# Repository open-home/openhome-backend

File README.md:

# OpenHome Backend

# Build
Run `npm run build` to build the backend.

# Running server
Navigate to `/dist` folder and run `node openhome-service.js`

# Docker deployment
Run `docker build -t image-name .` to build an image

Then you can get your container running:

`docker run -d -p 8080:8080 -p 3000:3000 -p 3001:3001 --name container-name image-name`

# Docker-compose deployment
Run `npm run-script docker` or `docker-compose up -d` to start the cluster of `openhome-backend` and `openhome-panel`

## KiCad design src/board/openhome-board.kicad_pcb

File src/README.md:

# OpenHome Backend

# Build
Run `npm run build` to build the backend.

# Running server
Navigate to `/dist` folder and run `node openhome-service.js`

# Docker deployment
Run `docker build -t image-name .` to build an image

Then you can get your container running:

`docker run -d -p 8080:8080 -p 3000:3000 -p 3001:3001 --name container-name image-name`

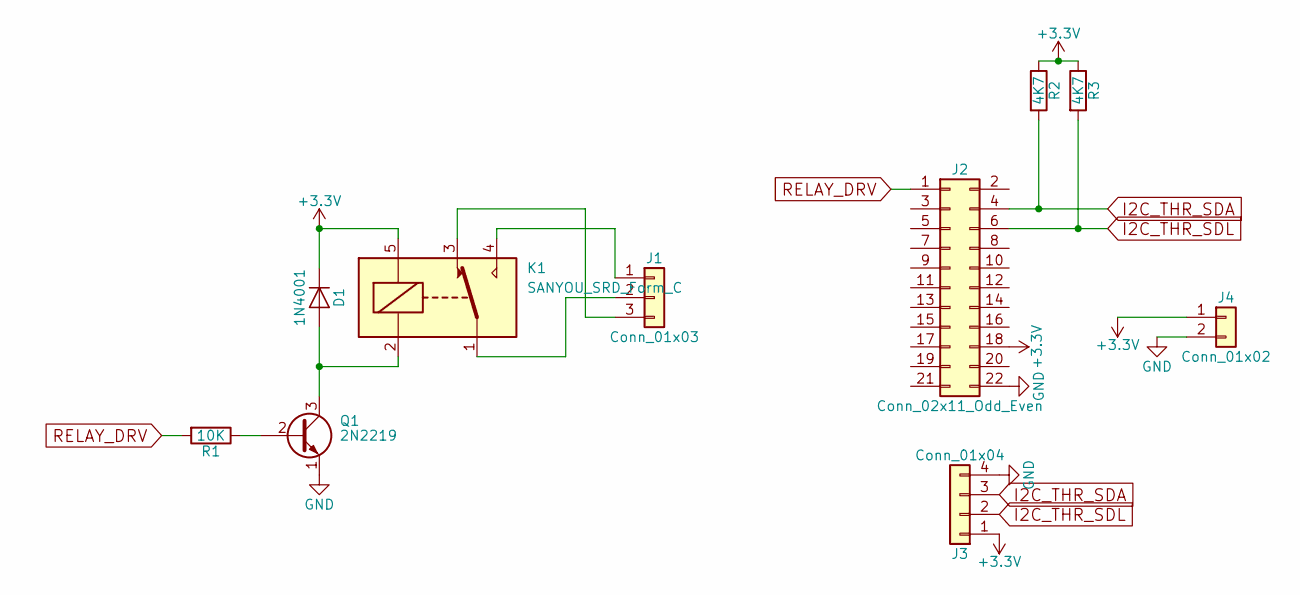
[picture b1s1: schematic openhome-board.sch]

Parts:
D1: 1N4001; D_DO-41_SOD81_Horizontal_RM10
J1: Conn_01x03; bornier3
J2: Conn_02x11_Odd_Even; ESPRUINO_WIFI
J3: Conn_01x04; SL-104-X-XX_1x04
J4: Conn_01x02
K1: SANYOU_SRD_Form_C; Relay_SPDT_SANYOU_SRD_Series_Form_C
Q1: 2N2219; TO-39-3
R1: 10K; R_Axial_DIN0207_L6.3mm_D2.5mm_P10.16mm_Horizontal
R2, R3: 4K7; R_Axial_DIN0207_L6.3mm_D2.5mm_P10.16mm_Horizontal

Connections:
+3V3: D1.1 (K), J2.18, J3.1, J4.1, K1.5, R2.1, R3.1
GND: J2.22, J3.4, J4.2, Q1.1 (E)
I2C_THR_SDA: J2.4, J3.3, R2.2
I2C_THR_SDL: J2.6, J3.2, R3.2
unnamed: D1.2 (A), K1.2, Q1.3 (C)
unnamed: J1.1, K1.4
unnamed: J1.2, K1.1
unnamed: J1.3, K1.3
unnamed: Q1.2 (B), R1.1
RELAY_DRV: J2.1, R1.2

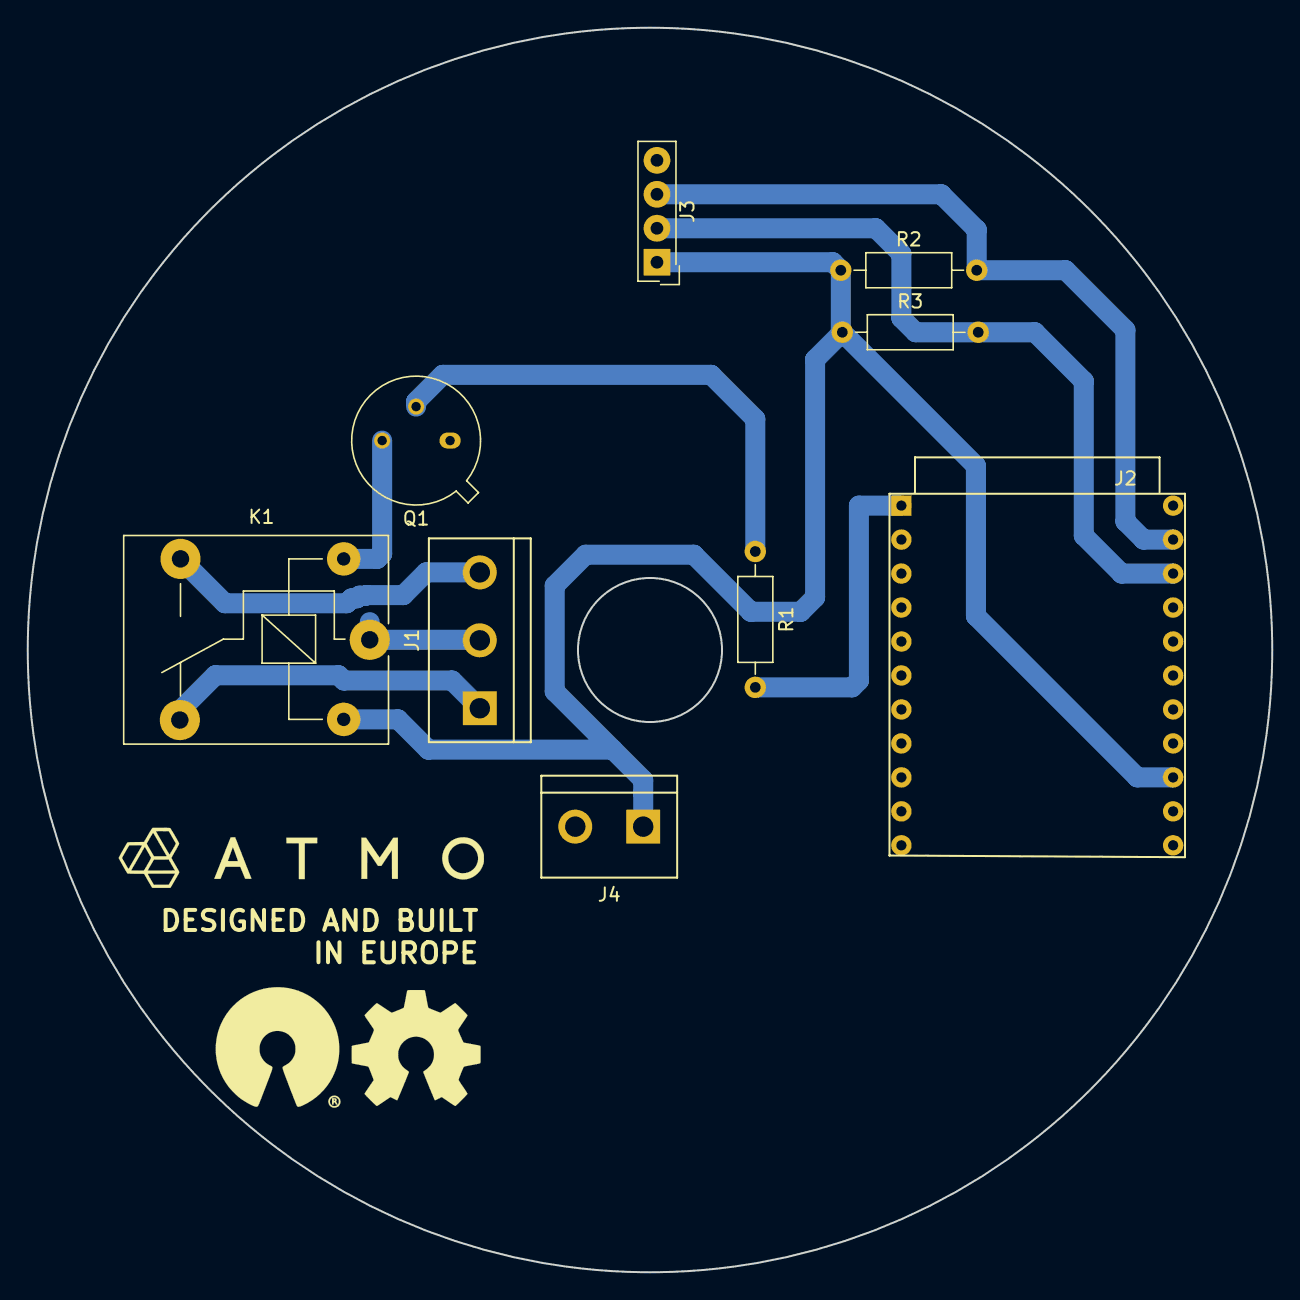
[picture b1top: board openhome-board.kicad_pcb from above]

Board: 2 copper layers, 93.1 x 93.1 mm, 9 parts (0 on the bottom side), 10 nets.

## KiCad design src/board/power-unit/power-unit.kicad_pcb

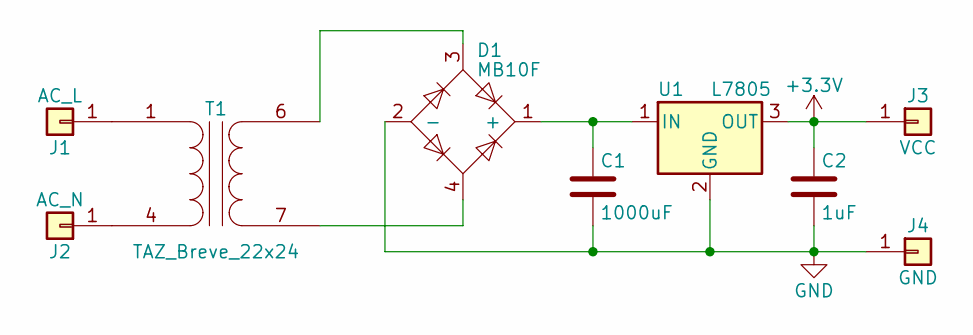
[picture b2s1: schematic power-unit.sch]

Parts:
C1: 1000uF; C_Radial_D8_L13_P3.8
C2: 1uF; C_Radial_D10_L16_P5
D1: MB10F; Diode_Bridge_TO-269AA
J1: AC_L; 1pin
J2: AC_N; 1pin
J3: VCC; 1pin
J4: GND; 1pin
T1: TAZ_Breve_22x24; Transformer_Breve_TEZ-22x24
U1: L7805; TO-220-3_Vertical

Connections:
+3V3: C2.1, J3.1, U1.3 (OUT)
GND: C1.2, C2.2, D1.2 (-), J4.1, U1.2 (GND)
unnamed: C1.1, D1.1 (+), U1.1 (IN)
unnamed: D1.3, T1.6 (SB)
unnamed: D1.4, T1.7 (SA)
unnamed: J1.1, T1.1 (AA)
unnamed: J2.1, T1.4 (AB)

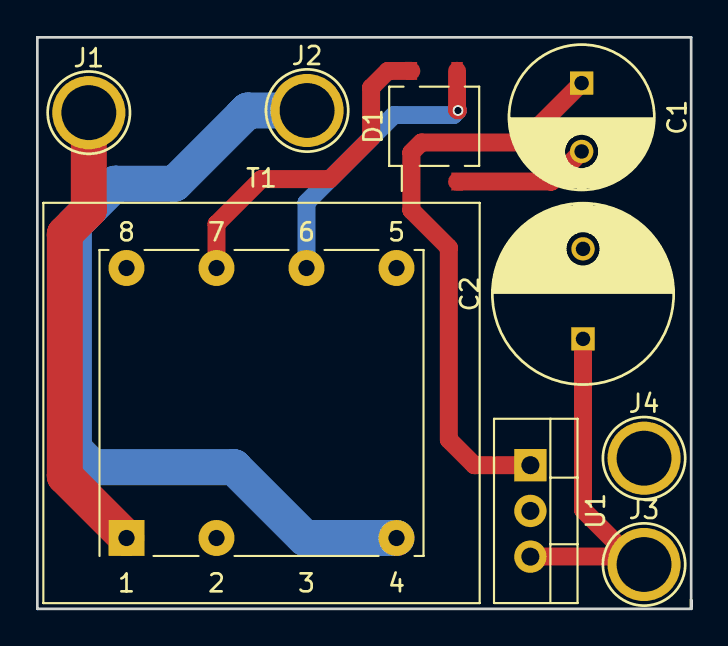
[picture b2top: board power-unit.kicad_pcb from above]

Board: 2 copper layers, 36.3 x 31.7 mm, 9 parts (0 on the bottom side), 7 nets.

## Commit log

2018-04-22 removed test mode
2018-04-28 Project general refactor
2018-05-05 Added power unit board, thermostat board and firmware
2018-05-05 Added README, created Dockerfile for Docker deployment
2018-05-05 forwarding thermostat
2018-05-05 no test mode
2018-05-05 fixed thermostat
2018-05-05 Added port mapping in Dockerfile
2018-05-05 Added docker-compose configuration, updated README
2018-05-06 docker compose fix
2018-05-07 Corrected Dockerfile and README
2018-05-07 correct some comments + board
2018-05-12 completing thermostat
2018-05-13 refactoring devices
